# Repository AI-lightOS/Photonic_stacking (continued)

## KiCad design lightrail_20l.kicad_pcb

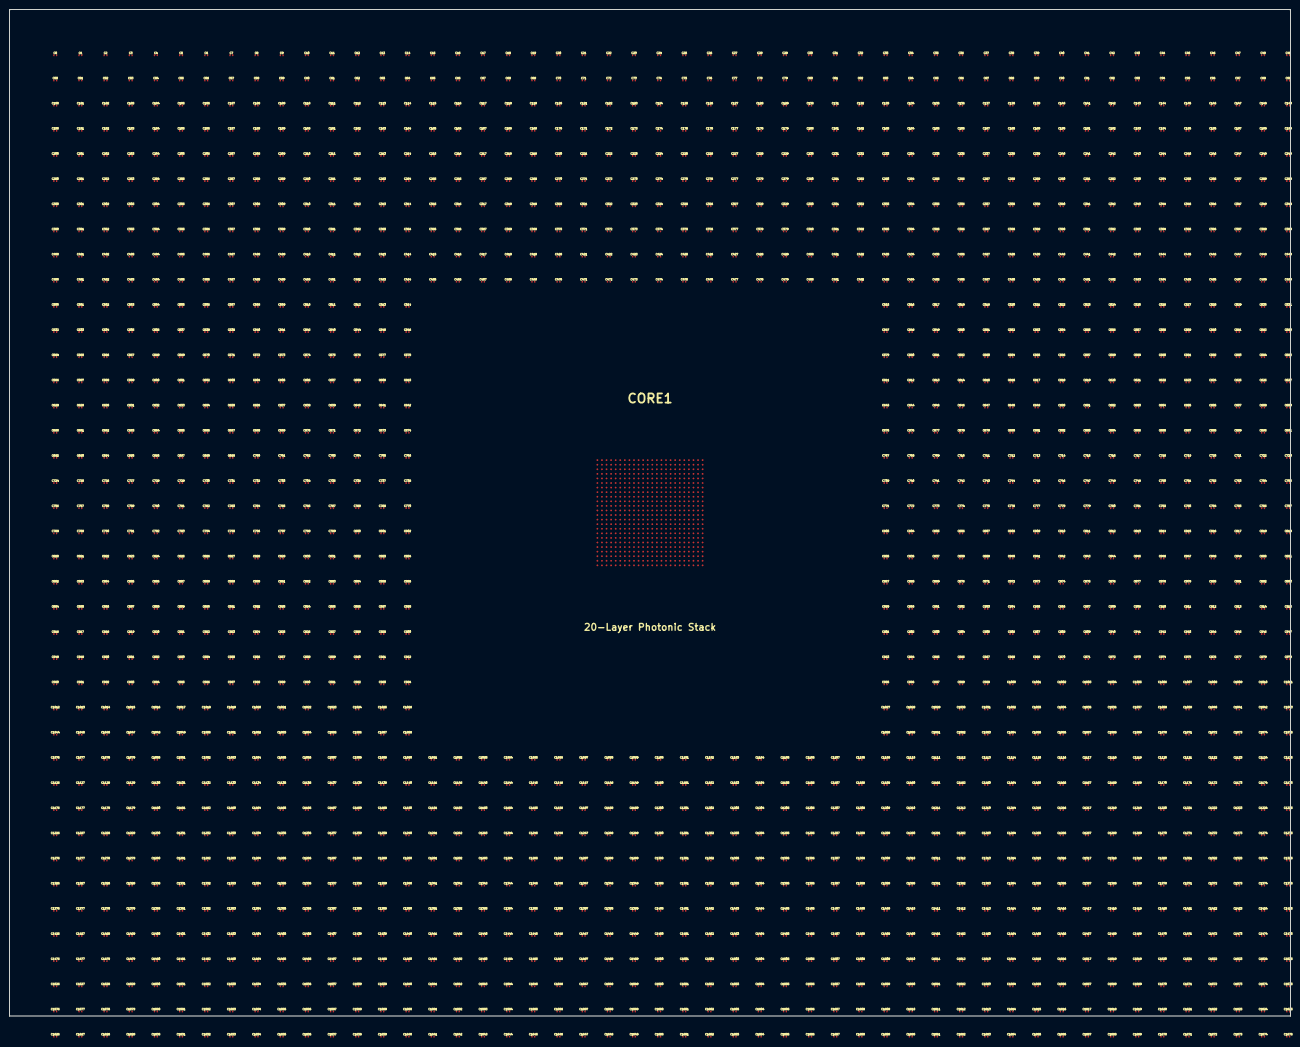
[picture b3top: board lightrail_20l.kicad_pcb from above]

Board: 20 copper layers, 280.0 x 220.0 mm, 1677 parts (0 on the bottom side), 235 nets, no tracks yet.

Parts:
C0, C1, C2, C3, C4, C5, C6, C7, C8, C9, C10, C11, C12, C13, C14, C15, C16, C17, C18, C19, C20, C21, C22, C23, C24, C25, C26, C27, C28, C29, C30, C31, C32, C33, C34, C35, C36, C37, C38, C39, C40, C41, C42, C43, C44, C45, C46, C47, C48, C49, C50, C51, C52, C53, C54, C55, C56, C57, C58, C59, C60, C61, C62, C63, C64, C65, C66, C67, C68, C69, C70, C71, C72, C73, C74, C75, C76, C77, C78, C79, C80, C81, C82, C83, C84, C85, C86, C87, C88, C89, C90, C91, C92, C93, C94, C95, C96, C97, C98, C99, C100, C101, C102, C103, C104, C105, C106, C107, C108, C109, C110, C111, C112, C113, C114, C115, C116, C117, C118, C119, C120, C121, C122, C123, C124, C125, C126, C127, C128, C129, C130, C131, C132, C133, C134, C135, C136, C137, C138, C139, C140, C141, C142, C143, C144, C145, C146, C147, C148, C149, C150, C151, C152, C153, C154, C155, C156, C157, C158, C159, C160, C161, C162, C163, C164, C165, C166, C167, C168, C169, C170, C171, C172, C173, C174, C175, C176, C177, C178, C179, C180, C181, C182, C183, C184, C185, C186, C187, C188, C189, C190, C191, C192, C193, C194, C195, C196, C197, C198, C199, C200, C201, C202, C203, C204, C205, C206, C207, C208, C209, C210, C211, C212, C213, C214, C215, C216, C217, C218, C219, C220, C221, C222, C223, C224, C225, C226, C227, C228, C229, C230, C231, C232, C233, C234, C235, C236, C237, C238, C239, C240, C241, C242, C243, C244, C245, C246, C247, C248, C249, C250, C251, C252, C253, C254, C255, C256, C257, C258, C259, C260, C261, C262, C263, C264, C265, C266, C267, C268, C269, C270, C271, C272, C273, C274, C275, C276, C277, C278, C279, C280, C281, C282, C283, C284, C285, C286, C287, C288, C289, C290, C291, C292, C293, C294, C295, C296, C297, C298, C299, C300, C301, C302, C303, C304, C305, C306, C307, C308, C309, C310, C311, C312, C313, C314, C315, C316, C317, C318, C319, C320, C321, C322, C323, C324, C325, C326, C327, C328, C329, C330, C331, C332, C333, C334, C335, C336, C337, C338, C339, C340, C341, C342, C343, C344, C345, C346, C347, C348, C349, C350, C351, C352, C353, C354, C355, C356, C357, C358, C359, C360, C361, C362, C363, C364, C365, C366, C367, C368, C369, C370, C371, C372, C373, C374, C375, C376, C377, C378, C379, C380, C381, C382, C383, C384, C385, C386, C387, C388, C389, C390, C391, C392, C393, C394, C395, C396, C397, C398, C399, C400, C401, C402, C403, C404, C405, C406, C407, C408, C409, C410, C411, C412, C413, C414, C415, C416, C417, C418, C419, C420, C421, C422, C423, C424, C425, C426, C427, C428, C429, C430, C431, C432, C433, C434, C435, C436, C437, C438, C439, C440, C441, C442, C443, C444, C445, C446, C447, C448, C449, C450, C451, C452, C453, C454, C455, C456, C457, C458, C459, C460, C461, C462, C463, C464, C465, C466, C467, C468, C469, C470, C471, C472, C473, C474, C475, C476, C477, C478, C479, C480, C481, C482, C483, C484, C485, C486, C487, C488, C489, C490, C491, C492, C493, C494, C495, C496, C497, C498, C499, C500, C501, C502, C503, C504, C505, C506, C507, C508, C509, C510, C511, C512, C513, C514, C515, C516, C517, C518, C519, C520, C521, C522, C523, C524, C525, C526, C527, C528, C529, C530, C531, C532, C533, C534, C535, C536, C537, C538, C539, C540, C541, C542, C543, C544, C545, C546, C547, C548, C549, C550, C551, C552, C553, C554, C555, C556, C557, C558, C559, C560, C561, C562, C563, C564, C565, C566, C567, C568, C569, C570, C571, C572, C573, C574, C575, C576, C577, C578, C579, C580, C581, C582, C583, C584, C585, C586, C587, C588, C589, C590, C591, C592, C593, C594, C595, C596, C597, C598, C599, C600, C601, C602, C603, C604, C605, C606, C607, C608, C609, C610, C611, C612, C613, C614, C615, C616, C617, C618, C619, C620, C621, C622, C623, C624, C625, C626, C627, C628, C629, C630, C631, C632, C633, C634, C635, C636, C637, C638, C639, C640, C641, C642, C643, C644, C645, C646, C647, C648, C649, C650, C651, C652, C653, C654, C655, C656, C657, C658, C659, C660, C661, C662, C663, C664, C665, C666, C667, C668, C669, C670, C671, C672, C673, C674, C675, C676, C677, C678, C679, C680, C681, C682, C683, C684, C685, C686, C687, C688, C689, C690, C691, C692, C693, C694, C695, C696, C697, C698, C699, C700, C701, C702, C703, C704, C705, C706, C707, C708, C709, C710, C711, C712, C713, C714, C715, C716, C717, C718, C719, C720, C721, C722, C723, C724, C725, C726, C727, C728, C729, C730, C731, C732, C733, C734, C735, C736, C737, C738, C739, C740, C741, C742, C743, C744, C745, C746, C747, C748, C749, C750, C751, C752, C753, C754, C755, C756, C757, C758, C759, C760, C761, C762, C763, C764, C765, C766, C767, C768, C769, C770, C771, C772, C773, C774, C775, C776, C777, C778, C779, C780, C781, C782, C783, C784, C785, C786, C787, C788, C789, C790, C791, C792, C793, C794, C795, C796, C797, C798, C799, C800, C801, C802, C803, C804, C805, C806, C807, C808, C809, C810, C811, C812, C813, C814, C815, C816, C817, C818, C819, C820, C821, C822, C823, C824, C825, C826, C827, C828, C829, C830, C831, C832, C833, C834, C835, C836, C837, C838, C839, C840, C841, C842, C843, C844, C845, C846, C847, C848, C849, C850, C851, C852, C853, C854, C855, C856, C857, C858, C859, C860, C861, C862, C863, C864, C865, C866, C867, C868, C869, C870, C871, C872, C873, C874, C875, C876, C877, C878, C879, C880, C881, C882, C883, C884, C885, C886, C887, C888, C889, C890, C891, C892, C893, C894, C895, C896, C897, C898, C899, C900, C901, C902, C903, C904, C905, C906, C907, C908, C909, C910, C911, C912, C913, C914, C915, C916, C917, C918, C919, C920, C921, C922, C923, C924, C925, C926, C927, C928, C929, C930, C931, C932, C933, C934, C935, C936, C937, C938, C939, C940, C941, C942, C943, C944, C945, C946, C947, C948, C949, C950, C951, C952, C953, C954, C955, C956, C957, C958, C959, C960, C961, C962, C963, C964, C965, C966, C967, C968, C969, C970, C971, C972, C973, C974, C975, C976, C977, C978, C979, C980, C981, C982, C983, C984, C985, C986, C987, C988, C989, C990, C991, C992, C993, C994, C995, C996, C997, C998, C999, C1000, C1001, C1002, C1003, C1004, C1005, C1006, C1007, C1008, C1009, C1010, C1011, C1012, C1013, C1014, C1015, C1016, C1017, C1018, C1019, C1020, C1021, C1022, C1023, C1024, C1025, C1026, C1027, C1028, C1029, C1030, C1031, C1032, C1033, C1034, C1035, C1036, C1037, C1038, C1039, C1040, C1041, C1042, C1043, C1044, C1045, C1046, C1047, C1048, C1049, C1050, C1051, C1052, C1053, C1054, C1055, C1056, C1057, C1058, C1059, C1060, C1061, C1062, C1063, C1064, C1065, C1066, C1067, C1068, C1069, C1070, C1071, C1072, C1073, C1074, C1075, C1076, C1077, C1078, C1079, C1080, C1081, C1082, C1083, C1084, C1085, C1086, C1087, C1088, C1089, C1090, C1091, C1092, C1093, C1094, C1095, C1096, C1097, C1098, C1099, C1100, C1101, C1102, C1103, C1104, C1105, C1106, C1107, C1108, C1109, C1110, C1111, C1112, C1113, C1114, C1115, C1116, C1117, C1118, C1119, C1120, C1121, C1122, C1123, C1124, C1125, C1126, C1127, C1128, C1129, C1130, C1131, C1132, C1133, C1134, C1135, C1136, C1137, C1138, C1139, C1140, C1141, C1142, C1143, C1144, C1145, C1146, C1147, C1148, C1149, C1150, C1151, C1152, C1153, C1154, C1155, C1156, C1157, C1158, C1159, C1160, C1161, C1162, C1163, C1164, C1165, C1166, C1167, C1168, C1169, C1170, C1171, C1172, C1173, C1174, C1175, C1176, C1177, C1178, C1179, C1180, C1181, C1182, C1183, C1184, C1185, C1186, C1187, C1188, C1189, C1190, C1191, C1192, C1193, C1194, C1195, C1196, C1197, C1198, C1199, C1200, C1201, C1202, C1203, C1204, C1205, C1206, C1207, C1208, C1209, C1210, C1211, C1212, C1213, C1214, C1215, C1216, C1217, C1218, C1219, C1220, C1221, C1222, C1223, C1224, C1225, C1226, C1227, C1228, C1229, C1230, C1231, C1232, C1233, C1234, C1235, C1236, C1237, C1238, C1239, C1240, C1241, C1242, C1243, C1244, C1245, C1246, C1247, C1248, C1249, C1250, C1251, C1252, C1253, C1254, C1255, C1256, C1257, C1258, C1259, C1260, C1261, C1262, C1263, C1264, C1265, C1266, C1267, C1268, C1269, C1270, C1271, C1272, C1273, C1274, C1275, C1276, C1277, C1278, C1279, C1280, C1281, C1282, C1283, C1284, C1285, C1286, C1287, C1288, C1289, C1290, C1291, C1292, C1293, C1294, C1295, C1296, C1297, C1298, C1299, C1300, C1301, C1302, C1303, C1304, C1305, C1306, C1307, C1308, C1309, C1310, C1311, C1312, C1313, C1314, C1315, C1316, C1317, C1318, C1319, C1320, C1321, C1322, C1323, C1324, C1325, C1326, C1327, C1328, C1329, C1330, C1331, C1332, C1333, C1334, C1335, C1336, C1337, C1338, C1339, C1340, C1341, C1342, C1343, C1344, C1345, C1346, C1347, C1348, C1349, C1350, C1351, C1352, C1353, C1354, C1355, C1356, C1357, C1358, C1359, C1360, C1361, C1362, C1363, C1364, C1365, C1366, C1367, C1368, C1369, C1370, C1371, C1372, C1373, C1374, C1375, C1376, C1377, C1378, C1379, C1380, C1381, C1382, C1383, C1384, C1385, C1386, C1387, C1388, C1389, C1390, C1391, C1392, C1393, C1394, C1395, C1396, C1397, C1398, C1399, C1400, C1401, C1402, C1403, C1404, C1405, C1406, C1407, C1408, C1409, C1410, C1411, C1412, C1413, C1414, C1415, C1416, C1417, C1418, C1419, C1420, C1421, C1422, C1423, C1424, C1425, C1426, C1427, C1428, C1429, C1430, C1431, C1432, C1433, C1434, C1435, C1436, C1437, C1438, C1439, C1440, C1441, C1442, C1443, C1444, C1445, C1446, C1447, C1448, C1449, C1450, C1451, C1452, C1453, C1454, C1455, C1456, C1457, C1458, C1459, C1460, C1461, C1462, C1463, C1464, C1465, C1466, C1467, C1468, C1469, C1470, C1471, C1472, C1473, C1474, C1475, C1476, C1477, C1478, C1479, C1480, C1481, C1482, C1483, C1484, C1485, C1486, C1487, C1488, C1489, C1490, C1491, C1492, C1493, C1494, C1495, C1496, C1497, C1498, C1499, C1500, C1501, C1502, C1503, C1504, C1505, C1506, C1507, C1508, C1509, C1510, C1511, C1512, C1513, C1514, C1515, C1516, C1517, C1518, C1519, C1520, C1521, C1522, C1523, C1524, C1525, C1526, C1527, C1528, C1529, C1530, C1531, C1532, C1533, C1534, C1535, C1536, C1537, C1538, C1539, C1540, C1541, C1542, C1543, C1544, C1545, C1546, C1547, C1548, C1549, C1550, C1551, C1552, C1553, C1554, C1555, C1556, C1557, C1558, C1559, C1560, C1561, C1562, C1563, C1564, C1565, C1566, C1567, C1568, C1569, C1570, C1571, C1572, C1573, C1574, C1575, C1576, C1577, C1578, C1579, C1580, C1581, C1582, C1583, C1584, C1585, C1586, C1587, C1588, C1589, C1590, C1591, C1592, C1593, C1594, C1595, C1596, C1597, C1598, C1599, C1600, C1601, C1602, C1603, C1604, C1605, C1606, C1607, C1608, C1609, C1610, C1611, C1612, C1613, C1614, C1615, C1616, C1617, C1618, C1619, C1620, C1621, C1622, C1623, C1624, C1625, C1626, C1627, C1628, C1629, C1630, C1631, C1632, C1633, C1634, C1635, C1636, C1637, C1638, C1639, C1640, C1641, C1642, C1643, C1644, C1645, C1646, C1647, C1648, C1649, C1650, C1651, C1652, C1653, C1654, C1655, C1656, C1657, C1658, C1659, C1660, C1661, C1662, C1663, C1664, C1665, C1666, C1667, C1668, C1669, C1670, C1671, C1672, C1673, C1674, C1675: C_0201_0603Metric
CORE1: 20-Layer Photonic Stack; IntelligenceStack_20L

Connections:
GND: C0.2, C1.1, C1.2, C2.2, C3.2, C4.2, C5.1, C5.2, C6.2, C7.2, C8.2, C9.1, C9.2, C10.1, C10.2, C11.1, C11.2, C12.2, C13.2, C14.2, C15.1, C15.2, C16.1, C16.2, C17.2, C18.2, C19.1, C19.2, C20.1, C20.2, C21.1, C21.2, C22.2, C23.1, C23.2, C24.2, C25.2, C26.1, C26.2, C27.2, C28.2, C29.2, C30.2, C31.2, C32.2, C33.2, C34.2, C35.1, C35.2, C36.1, C36.2, C37.1, C37.2, C38.1, C38.2, C39.2, C40.2, C41.2, C42.2, C43.2, C44.1, C44.2, C45.1, C45.2, C46.2, C47.1, C47.2, C48.2, C49.2, C50.1, C50.2, C51.2, C52.2, C53.2, C54.2, C55.1, C55.2, C56.1, C56.2, C57.2, C58.1, C58.2, C59.2, C60.2, C61.2, C62.1, C62.2, C63.2, C64.2, C65.1, C65.2, C66.2, C67.1, C67.2, C68.2, C69.1, C69.2, C70.2, C71.1, C71.2, C72.2, C73.2, C74.2, C75.2, C76.2, C77.1, C77.2, C78.2, C79.2, C80.2, C81.2, C82.1, C82.2, C83.2, C84.2, C85.2, C86.2, C87.2, C88.1, C88.2, C89.2, C90.2, C91.2, C92.1, C92.2, C93.2, C94.1, C94.2, C95.1, C95.2, C96.2, C97.2, C98.1, C98.2, C99.2, C100.2, C101.2, C102.2, C103.2, C104.1, C104.2, C105.2, C106.1, C106.2, C107.1, C107.2, C108.1, C108.2, C109.1, C109.2, C110.2, C111.2, C112.1, C112.2, C113.2, C114.2, C115.1, C115.2, C116.1, C116.2, C117.2, C118.2, C119.1, C119.2, C120.2, C121.2, C122.1, C122.2, C123.2, C124.1, C124.2, C125.2, C126.2, C127.1, C127.2, C128.2, C129.2, C130.2, C131.1, C131.2, C132.2, C133.2, C134.2, C135.2, C136.2, C137.2, C138.1, C138.2, C139.2, C140.1, C140.2, C141.2, C142.2, C143.1, C143.2, C144.2, C145.2, C146.1, C146.2, C147.2, C148.2, C149.2, C150.1, C150.2, C151.2, C152.1, C152.2, C153.1, C153.2, C154.2, C155.2, C156.2, C157.2, C158.2, C159.1, C159.2, C160.2, C161.1, C161.2, C162.2, C163.2, C164.2, C165.2, C166.2, C167.2, C168.2, C169.1, C169.2, C170.1, C170.2, C171.2, C172.2, C173.2, C174.2, C175.2, C176.2, C177.2, C178.2, C179.2, C180.2, C181.2, C182.2, C183.1, C183.2, C184.2, C185.2, C186.2, C187.1, C187.2, C188.1, C188.2, C189.1, C189.2, C190.1, C190.2, C191.2, C192.2, C193.2, C194.2, C195.2, C196.1, C196.2, C197.2, C198.2, C199.2, C200.1, C200.2, C201.1, C201.2, C202.2, C203.2, C204.2, C205.2, C206.2, C207.2, C208.2, C209.1, C209.2, C210.2, C211.2, C212.1, C212.2, C213.1, C213.2, C214.2, C215.2, C216.2, C217.1, C217.2, C218.1, C218.2, C219.2, C220.2, C221.2, C222.2, C223.2, C224.1, C224.2, C225.2, C226.2, C227.2, C228.2, C229.2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
V_ANALOG: C2.1, C4.1, C6.1, C7.1, C8.1, C13.1, C14.1, C17.1, C22.1, C31.1, C32.1, C33.1, C41.1, C48.1, C49.1, C52.1, C54.1, C61.1, C64.1, C68.1, C70.1, C72.1, C73.1, C74.1, C76.1, C79.1, C80.1, C81.1, C83.1, C87.1, C90.1, C96.1, C97.1, C99.1, C100.1, C105.1, C113.1, C118.1, C126.1, C129.1, C133.1, C139.1, C141.1, C142.1, C145.1, C149.1, C151.1, C154.1, C155.1, C156.1, C157.1, C158.1, C160.1, C162.1, C165.1, C166.1, C167.1, C168.1, C177.1, C178.1, C179.1, C180.1, C181.1, C185.1, C191.1, C195.1, C197.1, C198.1, C199.1, C205.1, C207.1, C208.1, C210.1, C214.1, C215.1, C219.1, C220.1, C221.1, C222.1, C225.1, C226.1, C228.1, C234.1, C235.1, C240.1, C241.1, C245.1, C255.1, C256.1, C259.1, C266.1, C269.1, C271.1, C275.1, C277.1, C278.1, C280.1, C282.1, C289.1, C290.1, C295.1, C299.1, C308.1, C310.1, C313.1, C314.1, C315.1, C316.1, C319.1, C322.1, C323.1, C327.1, C345.1, C346.1, C348.1, C351.1, C353.1, C358.1, C359.1, C360.1, C361.1, C364.1, C365.1, C367.1, C368.1, C371.1, C372.1, C375.1, C376.1, C378.1, C379.1, C380.1, C383.1, C385.1, C391.1, C393.1, C394.1, C397.1, C399.1, C400.1, C401.1, C402.1, C404.1, C405.1, C407.1, C409.1, C410.1, C414.1, C415.1, C418.1, C420.1, C424.1, C427.1, C428.1, C431.1, C434.1, C437.1, C441.1, C443.1, C444.1, C445.1, C451.1, C453.1, C461.1, C466.1, C467.1, C468.1, C473.1, C479.1, C481.1, C485.1, C486.1, C490.1, C491.1, C493.1, C498.1, C501.1, C502.1, C505.1, C506.1, C509.1, C510.1, C513.1, C514.1, C521.1, C522.1, C523.1, C525.1, C535.1, C536.1, C539.1, C544.1, C546.1, C548.1, C559.1, C560.1, C562.1, C563.1, C567.1, C574.1, C575.1, C576.1, C579.1, C580.1, C581.1, C584.1, C585.1, C588.1, C590.1, C592.1, C593.1, C598.1, C599.1, C601.1, C604.1, C605.1, C611.1, C614.1, C616.1, C624.1, C627.1, C633.1, C634.1, C639.1, C640.1, C642.1, C644.1, C646.1, C647.1, C649.1, C653.1, C654.1, C659.1, C660.1, C661.1, C665.1, C669.1, C677.1, C679.1, C680.1, C681.1, C684.1, C685.1, C688.1, C689.1, C691.1, C692.1, C693.1, C695.1, C696.1, C703.1, C704.1, C706.1, C710.1, C714.1, C715.1, C717.1, C719.1, C722.1, C725.1, C726.1, C730.1, C731.1, C735.1, C745.1, C748.1, C752.1, C755.1, C756.1, C758.1, C759.1, C772.1, C775.1, C782.1, C785.1, C788.1, C793.1, C796.1, C797.1, C799.1, C802.1, C803.1, C804.1, C810.1, C813.1, C818.1, C819.1, C821.1, C827.1, C833.1, C835.1, C836.1, C837.1, C844.1, C847.1, C849.1, C850.1, C851.1, C852.1, C854.1, C857.1, C859.1, C863.1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
V_LIGHT: C0.1, C3.1, C12.1, C18.1, C24.1, C25.1, C27.1, C28.1, C29.1, C30.1, C34.1, C39.1, C40.1, C42.1, C43.1, C46.1, C51.1, C53.1, C57.1, C59.1, C60.1, C63.1, C66.1, C75.1, C78.1, C84.1, C85.1, C86.1, C89.1, C91.1, C93.1, C101.1, C102.1, C103.1, C110.1, C111.1, C114.1, C117.1, C120.1, C121.1, C123.1, C125.1, C128.1, C130.1, C132.1, C134.1, C135.1, C136.1, C137.1, C144.1, C147.1, C148.1, C163.1, C164.1, C171.1, C172.1, C173.1, C174.1, C175.1, C176.1, C182.1, C184.1, C186.1, C192.1, C193.1, C194.1, C202.1, C203.1, C204.1, C206.1, C211.1, C216.1, C223.1, C227.1, C229.1, C230.1, C231.1, C232.1, C233.1, C242.1, C246.1, C247.1, C249.1, C251.1, C253.1, C257.1, C258.1, C261.1, C263.1, C265.1, C268.1, C270.1, C272.1, C273.1, C276.1, C285.1, C286.1, C288.1, C292.1, C297.1, C298.1, C300.1, C302.1, C304.1, C306.1, C312.1, C317.1, C321.1, C325.1, C326.1, C328.1, C330.1, C331.1, C332.1, C335.1, C336.1, C337.1, C338.1, C341.1, C342.1, C343.1, C344.1, C347.1, C350.1, C355.1, C357.1, C363.1, C369.1, C381.1, C382.1, C384.1, C388.1, C390.1, C396.1, C403.1, C406.1, C408.1, C411.1, C423.1, C425.1, C426.1, C430.1, C432.1, C433.1, C435.1, C436.1, C446.1, C447.1, C452.1, C456.1, C457.1, C458.1, C460.1, C462.1, C463.1, C464.1, C469.1, C471.1, C474.1, C475.1, C476.1, C477.1, C480.1, C483.1, C487.1, C492.1, C494.1, C495.1, C497.1, C500.1, C503.1, C507.1, C511.1, C512.1, C515.1, C519.1, C520.1, C524.1, C528.1, C529.1, C531.1, C534.1, C538.1, C543.1, C549.1, C551.1, C552.1, C553.1, C555.1, C556.1, C558.1, C561.1, C564.1, C565.1, C566.1, C569.1, C572.1, C577.1, C578.1, C582.1, C586.1, C587.1, C600.1, C603.1, C606.1, C607.1, C613.1, C617.1, C618.1, C621.1, C622.1, C623.1, C625.1, C629.1, C635.1, C637.1, C641.1, C645.1, C648.1, C650.1, C651.1, C655.1, C656.1, C657.1, C658.1, C666.1, C667.1, C668.1, C670.1, C672.1, C673.1, C674.1, C675.1, C678.1, C682.1, C683.1, C698.1, C699.1, C701.1, C707.1, C709.1, C711.1, C713.1, C720.1, C721.1, C723.1, C724.1, C727.1, C728.1, C729.1, C732.1, C733.1, C734.1, C737.1, C738.1, C740.1, C743.1, C746.1, C751.1, C757.1, C762.1, C763.1, C764.1, C765.1, C770.1, C771.1, C773.1, C776.1, C777.1, C778.1, C779.1, C780.1, C781.1, C798.1, C805.1, C806.1, C809.1, C812.1, C814.1, C815.1, C816.1, C817.1, C825.1, C826.1, C830.1, C832.1, C834.1, C840.1, C843.1, C848.1, C853.1, C855.1, C856.1, C862.1, C864.1, C865.1, C877.1, C878.1, C881.1, C882.1, C886.1, C887.1, C890.1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
WAVE_BUS_0: CORE1.1, CORE1.257, CORE1.513
WAVE_BUS_1: CORE1.2, CORE1.258, CORE1.514
WAVE_BUS_2: CORE1.3, CORE1.259, CORE1.515
WAVE_BUS_3: CORE1.4, CORE1.260, CORE1.516
WAVE_BUS_4: CORE1.5, CORE1.261, CORE1.517
WAVE_BUS_5: CORE1.6, CORE1.262, CORE1.518
WAVE_BUS_6: CORE1.7, CORE1.263, CORE1.519
WAVE_BUS_7: CORE1.8, CORE1.264, CORE1.520
WAVE_BUS_8: CORE1.9, CORE1.265, CORE1.521
WAVE_BUS_9: CORE1.10, CORE1.266, CORE1.522
WAVE_BUS_10: CORE1.11, CORE1.267, CORE1.523
WAVE_BUS_11: CORE1.12, CORE1.268, CORE1.524
WAVE_BUS_12: CORE1.13, CORE1.269, CORE1.525
WAVE_BUS_13: CORE1.14, CORE1.270, CORE1.526
WAVE_BUS_14: CORE1.15, CORE1.271, CORE1.527
WAVE_BUS_15: CORE1.16, CORE1.272, CORE1.528
WAVE_BUS_16: CORE1.17, CORE1.273, CORE1.529
WAVE_BUS_17: CORE1.18, CORE1.530
WAVE_BUS_18: CORE1.19, CORE1.531
WAVE_BUS_19: CORE1.20, CORE1.532
WAVE_BUS_20: CORE1.21, CORE1.533
WAVE_BUS_21: CORE1.22, CORE1.534
WAVE_BUS_22: CORE1.23, CORE1.535
WAVE_BUS_23: CORE1.24, CORE1.280, CORE1.536
WAVE_BUS_24: CORE1.25, CORE1.281, CORE1.537
WAVE_BUS_25: CORE1.26, CORE1.282, CORE1.538
WAVE_BUS_26: CORE1.27, CORE1.283, CORE1.539
WAVE_BUS_27: CORE1.28, CORE1.284, CORE1.540
WAVE_BUS_28: CORE1.29, CORE1.285, CORE1.541
WAVE_BUS_29: CORE1.30, CORE1.286, CORE1.542
WAVE_BUS_30: CORE1.31, CORE1.287, CORE1.543
WAVE_BUS_31: CORE1.32, CORE1.288, CORE1.544
WAVE_BUS_32: CORE1.33, CORE1.289, CORE1.545
WAVE_BUS_33: CORE1.34, CORE1.290, CORE1.546
WAVE_BUS_34: CORE1.35, CORE1.291, CORE1.547
WAVE_BUS_35: CORE1.36, CORE1.292, CORE1.548
WAVE_BUS_36: CORE1.37, CORE1.293, CORE1.549
WAVE_BUS_37: CORE1.38, CORE1.294, CORE1.550
WAVE_BUS_38: CORE1.39, CORE1.295, CORE1.551
WAVE_BUS_39: CORE1.40, CORE1.296, CORE1.552
WAVE_BUS_40: CORE1.41, CORE1.297, CORE1.553
WAVE_BUS_41: CORE1.42, CORE1.554
WAVE_BUS_42: CORE1.43, CORE1.555
WAVE_BUS_43: CORE1.44, CORE1.556
WAVE_BUS_44: CORE1.45, CORE1.557
WAVE_BUS_45: CORE1.46, CORE1.558
WAVE_BUS_46: CORE1.47, CORE1.559
WAVE_BUS_47: CORE1.48, CORE1.304, CORE1.560
WAVE_BUS_48: CORE1.49, CORE1.305, CORE1.561
WAVE_BUS_49: CORE1.50, CORE1.306, CORE1.562
WAVE_BUS_50: CORE1.51, CORE1.307, CORE1.563
WAVE_BUS_51: CORE1.52, CORE1.308, CORE1.564
WAVE_BUS_52: CORE1.53, CORE1.309, CORE1.565
WAVE_BUS_53: CORE1.54, CORE1.310, CORE1.566
WAVE_BUS_54: CORE1.55, CORE1.311, CORE1.567
WAVE_BUS_55: CORE1.56, CORE1.312, CORE1.568
WAVE_BUS_56: CORE1.57, CORE1.313, CORE1.569
WAVE_BUS_57: CORE1.58, CORE1.314, CORE1.570
WAVE_BUS_58: CORE1.59, CORE1.315, CORE1.571
WAVE_BUS_59: CORE1.60, CORE1.316, CORE1.572
WAVE_BUS_60: CORE1.61, CORE1.317, CORE1.573
WAVE_BUS_61: CORE1.62, CORE1.318, CORE1.574
WAVE_BUS_62: CORE1.63, CORE1.319, CORE1.575
WAVE_BUS_63: CORE1.64, CORE1.320, CORE1.576
WAVE_BUS_64: CORE1.65, CORE1.321
WAVE_BUS_71: CORE1.72, CORE1.328
WAVE_BUS_72: CORE1.73, CORE1.329
WAVE_BUS_73: CORE1.74, CORE1.330
WAVE_BUS_74: CORE1.75, CORE1.331
WAVE_BUS_75: CORE1.76, CORE1.332
WAVE_BUS_76: CORE1.77, CORE1.333
WAVE_BUS_77: CORE1.78, CORE1.334
WAVE_BUS_78: CORE1.79, CORE1.335
WAVE_BUS_79: CORE1.80, CORE1.336
WAVE_BUS_80: CORE1.81, CORE1.337
WAVE_BUS_81: CORE1.82, CORE1.338
WAVE_BUS_82: CORE1.83, CORE1.339
WAVE_BUS_83: CORE1.84, CORE1.340
WAVE_BUS_84: CORE1.85, CORE1.341
WAVE_BUS_85: CORE1.86, CORE1.342
WAVE_BUS_86: CORE1.87, CORE1.343
WAVE_BUS_87: CORE1.88, CORE1.344
WAVE_BUS_88: CORE1.89, CORE1.345
WAVE_BUS_95: CORE1.96, CORE1.352
WAVE_BUS_96: CORE1.97, CORE1.353
WAVE_BUS_97: CORE1.98, CORE1.354
WAVE_BUS_98: CORE1.99, CORE1.355
WAVE_BUS_99: CORE1.100, CORE1.356
WAVE_BUS_100: CORE1.101, CORE1.357
WAVE_BUS_101: CORE1.102, CORE1.358
WAVE_BUS_102: CORE1.103, CORE1.359
WAVE_BUS_103: CORE1.104, CORE1.360
WAVE_BUS_104: CORE1.105, CORE1.361
WAVE_BUS_105: CORE1.106, CORE1.362
WAVE_BUS_106: CORE1.107, CORE1.363
WAVE_BUS_107: CORE1.108, CORE1.364
WAVE_BUS_108: CORE1.109, CORE1.365
WAVE_BUS_109: CORE1.110, CORE1.366
WAVE_BUS_110: CORE1.111, CORE1.367
WAVE_BUS_111: CORE1.112, CORE1.368
WAVE_BUS_112: CORE1.113, CORE1.369
WAVE_BUS_113: CORE1.114, CORE1.370
WAVE_BUS_114: CORE1.115, CORE1.371
WAVE_BUS_115: CORE1.116, CORE1.372
WAVE_BUS_116: CORE1.117, CORE1.373
WAVE_BUS_117: CORE1.118, CORE1.374
WAVE_BUS_118: CORE1.119, CORE1.375
WAVE_BUS_119: CORE1.120, CORE1.376
WAVE_BUS_120: CORE1.121, CORE1.377
WAVE_BUS_121: CORE1.122, CORE1.378
WAVE_BUS_122: CORE1.123, CORE1.379
WAVE_BUS_123: CORE1.124, CORE1.380
WAVE_BUS_124: CORE1.125, CORE1.381
WAVE_BUS_125: CORE1.126, CORE1.382
WAVE_BUS_126: CORE1.127, CORE1.383
WAVE_BUS_127: CORE1.128, CORE1.384
WAVE_BUS_128: CORE1.129, CORE1.385
WAVE_BUS_129: CORE1.130, CORE1.386
WAVE_BUS_130: CORE1.131, CORE1.387
WAVE_BUS_131: CORE1.132, CORE1.388
WAVE_BUS_132: CORE1.133, CORE1.389
WAVE_BUS_133: CORE1.134, CORE1.390
WAVE_BUS_134: CORE1.135, CORE1.391
WAVE_BUS_135: CORE1.136, CORE1.392
WAVE_BUS_136: CORE1.137, CORE1.393
WAVE_BUS_137: CORE1.138, CORE1.394
WAVE_BUS_138: CORE1.139, CORE1.395
WAVE_BUS_139: CORE1.140, CORE1.396
WAVE_BUS_140: CORE1.141, CORE1.397
WAVE_BUS_141: CORE1.142, CORE1.398
WAVE_BUS_142: CORE1.143, CORE1.399
WAVE_BUS_143: CORE1.144, CORE1.400
WAVE_BUS_144: CORE1.145, CORE1.401
WAVE_BUS_145: CORE1.146, CORE1.402
WAVE_BUS_146: CORE1.147, CORE1.403
WAVE_BUS_147: CORE1.148, CORE1.404
WAVE_BUS_148: CORE1.149, CORE1.405
WAVE_BUS_149: CORE1.150, CORE1.406
WAVE_BUS_150: CORE1.151, CORE1.407
WAVE_BUS_151: CORE1.152, CORE1.408
WAVE_BUS_152: CORE1.153, CORE1.409
WAVE_BUS_153: CORE1.154, CORE1.410
WAVE_BUS_154: CORE1.155, CORE1.411
WAVE_BUS_155: CORE1.156, CORE1.412
WAVE_BUS_156: CORE1.157, CORE1.413
WAVE_BUS_157: CORE1.158, CORE1.414
WAVE_BUS_158: CORE1.159, CORE1.415
WAVE_BUS_159: CORE1.160, CORE1.416
WAVE_BUS_160: CORE1.161, CORE1.417
WAVE_BUS_161: CORE1.162, CORE1.418
WAVE_BUS_162: CORE1.163, CORE1.419
WAVE_BUS_163: CORE1.164, CORE1.420
WAVE_BUS_164: CORE1.165, CORE1.421
WAVE_BUS_165: CORE1.166, CORE1.422
WAVE_BUS_166: CORE1.167, CORE1.423
WAVE_BUS_167: CORE1.168, CORE1.424
WAVE_BUS_168: CORE1.169, CORE1.425
WAVE_BUS_169: CORE1.170, CORE1.426
WAVE_BUS_170: CORE1.171, CORE1.427
WAVE_BUS_171: CORE1.172, CORE1.428
WAVE_BUS_172: CORE1.173, CORE1.429
WAVE_BUS_173: CORE1.174, CORE1.430
WAVE_BUS_174: CORE1.175, CORE1.431
WAVE_BUS_175: CORE1.176, CORE1.432
WAVE_BUS_176: CORE1.177, CORE1.433
WAVE_BUS_177: CORE1.178, CORE1.434
WAVE_BUS_178: CORE1.179, CORE1.435
WAVE_BUS_179: CORE1.180, CORE1.436
WAVE_BUS_180: CORE1.181, CORE1.437
WAVE_BUS_181: CORE1.182, CORE1.438
WAVE_BUS_182: CORE1.183, CORE1.439
WAVE_BUS_183: CORE1.184, CORE1.440
WAVE_BUS_184: CORE1.185, CORE1.441
WAVE_BUS_185: CORE1.186, CORE1.442
WAVE_BUS_186: CORE1.187, CORE1.443
WAVE_BUS_187: CORE1.188, CORE1.444
WAVE_BUS_188: CORE1.189, CORE1.445
WAVE_BUS_189: CORE1.190, CORE1.446
WAVE_BUS_190: CORE1.191, CORE1.447
WAVE_BUS_191: CORE1.192, CORE1.448
WAVE_BUS_192: CORE1.193, CORE1.449
WAVE_BUS_193: CORE1.194, CORE1.450
WAVE_BUS_194: CORE1.195, CORE1.451
WAVE_BUS_195: CORE1.196, CORE1.452
WAVE_BUS_196: CORE1.197, CORE1.453
WAVE_BUS_197: CORE1.198, CORE1.454
WAVE_BUS_198: CORE1.199, CORE1.455
WAVE_BUS_199: CORE1.200, CORE1.456
WAVE_BUS_200: CORE1.201, CORE1.457
WAVE_BUS_201: CORE1.202, CORE1.458
WAVE_BUS_202: CORE1.203, CORE1.459
WAVE_BUS_203: CORE1.204, CORE1.460
WAVE_BUS_204: CORE1.205, CORE1.461
WAVE_BUS_205: CORE1.206, CORE1.462
WAVE_BUS_206: CORE1.207, CORE1.463
WAVE_BUS_207: CORE1.208, CORE1.464
WAVE_BUS_208: CORE1.209, CORE1.465
WAVE_BUS_209: CORE1.210, CORE1.466
WAVE_BUS_210: CORE1.211, CORE1.467
WAVE_BUS_211: CORE1.212, CORE1.468
WAVE_BUS_212: CORE1.213, CORE1.469
WAVE_BUS_213: CORE1.214, CORE1.470
WAVE_BUS_214: CORE1.215, CORE1.471
WAVE_BUS_215: CORE1.216, CORE1.472
WAVE_BUS_216: CORE1.217, CORE1.473
WAVE_BUS_217: CORE1.218, CORE1.474
WAVE_BUS_218: CORE1.219, CORE1.475
WAVE_BUS_219: CORE1.220, CORE1.476
WAVE_BUS_220: CORE1.221, CORE1.477
WAVE_BUS_221: CORE1.222, CORE1.478
WAVE_BUS_222: CORE1.223, CORE1.479
WAVE_BUS_223: CORE1.224, CORE1.480
WAVE_BUS_224: CORE1.225, CORE1.481
WAVE_BUS_231: CORE1.232, CORE1.488
WAVE_BUS_232: CORE1.233, CORE1.489
WAVE_BUS_233: CORE1.234, CORE1.490
WAVE_BUS_234: CORE1.235, CORE1.491
WAVE_BUS_235: CORE1.236, CORE1.492
WAVE_BUS_236: CORE1.237, CORE1.493
WAVE_BUS_237: CORE1.238, CORE1.494
WAVE_BUS_238: CORE1.239, CORE1.495
WAVE_BUS_239: CORE1.240, CORE1.496
WAVE_BUS_240: CORE1.241, CORE1.497
WAVE_BUS_241: CORE1.242, CORE1.498
WAVE_BUS_242: CORE1.243, CORE1.499
WAVE_BUS_243: CORE1.244, CORE1.500
WAVE_BUS_244: CORE1.245, CORE1.501
WAVE_BUS_245: CORE1.246, CORE1.502
WAVE_BUS_246: CORE1.247, CORE1.503
WAVE_BUS_247: CORE1.248, CORE1.504
WAVE_BUS_248: CORE1.249, CORE1.505
WAVE_BUS_255: CORE1.256, CORE1.512

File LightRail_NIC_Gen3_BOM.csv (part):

Designator,Description,Manufacturer,MPN,Qty,Footprint
U1,TFLN-MZM-400G-C Modulator Array,LightRail-Optical,LR-TFLN-MZM-400G,1,TFLN_MZM_400G
U2,DFB Laser Source (CW-C-Band),Lumentum,LR-DFB-C-BAND,1,DFB_Laser_U2
U3,Sub-micron Waveguide Routing Core,LightRail-Silicon,LR-OPT-CORE-G3,1,Optical_Core_U3
U4,XPDV4120R High-Speed Photodetector Bank,Finisar,XPDV4120R,1,Detector_Bank_U4
U8,MPT5000 TEC Driver,Melexis,MPT5000,1,TEC_Driver_U8
U9,BCM84881 Controller (FPGA/SerDes),Broadcom,BCM84881,1,BCM84881_BGA
J1,PCIe Gen5 x16 Edge Connector,TE Connectivity,2013289-6,1,PCIe_x16_Edge
MPO1,MPO Input Fiber Array Connector,US Conec,MPO-12-IN,1,MPO_Array
MPO2,MPO Output Fiber Array Connector,US Conec,MPO-12-OUT,1,MPO_Array
C1,0603 MLCC 0.1uF 10V X5R,Murata,GRM188R61A104KA01D,1,C_0603_1608Metric
C2,0603 MLCC 0.1uF 10V X5R,Murata,GRM188R61A104KA01D,1,C_0603_1608Metric
C3,0603 MLCC 0.1uF 10V X5R,Murata,GRM188R61A104KA01D,1,C_0603_1608Metric
C4,0603 MLCC 0.1uF 10V X5R,Murata,GRM188R61A104KA01D,1,C_0603_1608Metric
C5,0603 MLCC 0.1uF 10V X5R,Murata,GRM188R61A104KA01D,1,C_0603_1608Metric
C6,0603 MLCC 0.1uF 10V X5R,Murata,GRM188R61A104KA01D,1,C_0603_1608Metric
C7,0603 MLCC 0.1uF 10V X5R,Murata,GRM188R61A104KA01D,1,C_0603_1608Metric
C8,0603 MLCC 0.1uF 10V X5R,Murata,GRM188R61A104KA01D,1,C_0603_1608Metric
C9,0603 MLCC 0.1uF 10V X5R,Murata,GRM188R61A104KA01D,1,C_0603_1608Metric
C10,0603 MLCC 0.1uF 10V X5R,Murata,GRM188R61A104KA01D,1,C_0603_1608Metric
C11,0603 MLCC 0.1uF 10V X5R,Murata,GRM188R61A104KA01D,1,C_0603_1608Metric
C12,0603 MLCC 0.1uF 10V X5R,Murata,GRM188R61A104KA01D,1,C_0603_1608Metric
C13,0603 MLCC 0.1uF 10V X5R,Murata,GRM188R61A104KA01D,1,C_0603_1608Metric
C14,0603 MLCC 0.1uF 10V X5R,Murata,GRM188R61A104KA01D,1,C_0603_1608Metric
C15,0603 MLCC 0.1uF 10V X5R,Murata,GRM188R61A104KA01D,1,C_0603_1608Metric
C16,0603 MLCC 0.1uF 10V X5R,Murata,GRM188R61A104KA01D,1,C_0603_1608Metric
C17,0603 MLCC 0.1uF 10V X5R,Murata,GRM188R61A104KA01D,1,C_0603_1608Metric
C18,0603 MLCC 0.1uF 10V X5R,Murata,GRM188R61A104KA01D,1,C_0603_1608Metric
C19,0603 MLCC 0.1uF 10V X5R,Murata,GRM188R61A104KA01D,1,C_0603_1608Metric
C20,0603 MLCC 0.1uF 10V X5R,Murata,GRM188R61A104KA01D,1,C_0603_1608Metric
C21,0603 MLCC 0.1uF 10V X5R,Murata,GRM188R61A104KA01D,1,C_0603_1608Metric
C22,0603 MLCC 0.1uF 10V X5R,Murata,GRM188R61A104KA01D,1,C_0603_1608Metric
C23,0603 MLCC 0.1uF 10V X5R,Murata,GRM188R61A104KA01D,1,C_0603_1608Metric
C24,0603 MLCC 0.1uF 10V X5R,Murata,GRM188R61A104KA01D,1,C_0603_1608Metric
C25,0603 MLCC 0.1uF 10V X5R,Murata,GRM188R61A104KA01D,1,C_0603_1608Metric
C26,0603 MLCC 0.1uF 10V X5R,Murata,GRM188R61A104KA01D,1,C_0603_1608Metric
C27,0603 MLCC 0.1uF 10V X5R,Murata,GRM188R61A104KA01D,1,C_0603_1608Metric
C28,0603 MLCC 0.1uF 10V X5R,Murata,GRM188R61A104KA01D,1,C_0603_1608Metric
C29,0603 MLCC 0.1uF 10V X5R,Murata,GRM188R61A104KA01D,1,C_0603_1608Metric
C30,0603 MLCC 0.1uF 10V X5R,Murata,GRM188R61A104KA01D,1,C_0603_1608Metric
C31,0603 MLCC 0.1uF 10V X5R,Murata,GRM188R61A104KA01D,1,C_0603_1608Metric
C32,0603 MLCC 0.1uF 10V X5R,Murata,GRM188R61A104KA01D,1,C_0603_1608Metric
C33,0603 MLCC 0.1uF 10V X5R,Murata,GRM188R61A104KA01D,1,C_0603_1608Metric
C34,0603 MLCC 0.1uF 10V X5R,Murata,GRM188R61A104KA01D,1,C_0603_1608Metric
C35,0603 MLCC 0.1uF 10V X5R,Murata,GRM188R61A104KA01D,1,C_0603_1608Metric
C36,0603 MLCC 0.1uF 10V X5R,Murata,GRM188R61A104KA01D,1,C_0603_1608Metric
C37,0603 MLCC 0.1uF 10V X5R,Murata,GRM188R61A104KA01D,1,C_0603_1608Metric
C38,0603 MLCC 0.1uF 10V X5R,Murata,GRM188R61A104KA01D,1,C_0603_1608Metric
C39,0603 MLCC 0.1uF 10V X5R,Murata,GRM188R61A104KA01D,1,C_0603_1608Metric
C40,0603 MLCC 0.1uF 10V X5R,Murata,GRM188R61A104KA01D,1,C_0603_1608Metric
C41,0603 MLCC 0.1uF 10V X5R,Murata,GRM188R61A104KA01D,1,C_0603_1608Metric
C42,0603 MLCC 0.1uF 10V X5R,Murata,GRM188R61A104KA01D,1,C_0603_1608Metric
C43,0603 MLCC 0.1uF 10V X5R,Murata,GRM188R61A104KA01D,1,C_0603_1608Metric
C44,0603 MLCC 0.1uF 10V X5R,Murata,GRM188R61A104KA01D,1,C_0603_1608Metric
C45,0603 MLCC 0.1uF 10V X5R,Murata,GRM188R61A104KA01D,1,C_0603_1608Metric
C46,0603 MLCC 0.1uF 10V X5R,Murata,GRM188R61A104KA01D,1,C_0603_1608Metric
C47,0603 MLCC 0.1uF 10V X5R,Murata,GRM188R61A104KA01D,1,C_0603_1608Metric
C48,0603 MLCC 0.1uF 10V X5R,Murata,GRM188R61A104KA01D,1,C_0603_1608Metric
C49,0603 MLCC 0.1uF 10V X5R,Murata,GRM188R61A104KA01D,1,C_0603_1608Metric
C50,0603 MLCC 0.1uF 10V X5R,Murata,GRM188R61A104KA01D,1,C_0603_1608Metric
C51,0603 MLCC 0.1uF 10V X5R,Murata,GRM188R61A104KA01D,1,C_0603_1608Metric
C52,0603 MLCC 0.1uF 10V X5R,Murata,GRM188R61A104KA01D,1,C_0603_1608Metric
C53,0603 MLCC 0.1uF 10V X5R,Murata,GRM188R61A104KA01D,1,C_0603_1608Metric
C54,0603 MLCC 0.1uF 10V X5R,Murata,GRM188R61A104KA01D,1,C_0603_1608Metric
C55,0603 MLCC 0.1uF 10V X5R,Murata,GRM188R61A104KA01D,1,C_0603_1608Metric
C56,0603 MLCC 0.1uF 10V X5R,Murata,GRM188R61A104KA01D,1,C_0603_1608Metric
C57,0603 MLCC 0.1uF 10V X5R,Murata,GRM188R61A104KA01D,1,C_0603_1608Metric
C58,0603 MLCC 0.1uF 10V X5R,Murata,GRM188R61A104KA01D,1,C_0603_1608Metric
C59,0603 MLCC 0.1uF 10V X5R,Murata,GRM188R61A104KA01D,1,C_0603_1608Metric
C60,0603 MLCC 0.1uF 10V X5R,Murata,GRM188R61A104KA01D,1,C_0603_1608Metric
C61,0603 MLCC 0.1uF 10V X5R,Murata,GRM188R61A104KA01D,1,C_0603_1608Metric
C62,0603 MLCC 0.1uF 10V X5R,Murata,GRM188R61A104KA01D,1,C_0603_1608Metric
C63,0603 MLCC 0.1uF 10V X5R,Murata,GRM188R61A104KA01D,1,C_0603_1608Metric
C64,0603 MLCC 0.1uF 10V X5R,Murata,GRM188R61A104KA01D,1,C_0603_1608Metric
C65,0603 MLCC 0.1uF 10V X5R,Murata,GRM188R61A104KA01D,1,C_0603_1608Metric
C66,0603 MLCC 0.1uF 10V X5R,Murata,GRM188R61A104KA01D,1,C_0603_1608Metric
C67,0603 MLCC 0.1uF 10V X5R,Murata,GRM188R61A104KA01D,1,C_0603_1608Metric
C68,0603 MLCC 0.1uF 10V X5R,Murata,GRM188R61A104KA01D,1,C_0603_1608Metric
C69,0603 MLCC 0.1uF 10V X5R,Murata,GRM188R61A104KA01D,1,C_0603_1608Metric
C70,0603 MLCC 0.1uF 10V X5R,Murata,GRM188R61A104KA01D,1,C_0603_1608Metric
C71,0603 MLCC 0.1uF 10V X5R,Murata,GRM188R61A104KA01D,1,C_0603_1608Metric
C72,0603 MLCC 0.1uF 10V X5R,Murata,GRM188R61A104KA01D,1,C_0603_1608Metric
C73,0603 MLCC 0.1uF 10V X5R,Murata,GRM188R61A104KA01D,1,C_0603_1608Metric
C74,0603 MLCC 0.1uF 10V X5R,Murata,GRM188R61A104KA01D,1,C_0603_1608Metric
C75,0603 MLCC 0.1uF 10V X5R,Murata,GRM188R61A104KA01D,1,C_0603_1608Metric
C76,0603 MLCC 0.1uF 10V X5R,Murata,GRM188R61A104KA01D,1,C_0603_1608Metric
C77,0603 MLCC 0.1uF 10V X5R,Murata,GRM188R61A104KA01D,1,C_0603_1608Metric
C78,0603 MLCC 0.1uF 10V X5R,Murata,GRM188R61A104KA01D,1,C_0603_1608Metric
C79,0603 MLCC 0.1uF 10V X5R,Murata,GRM188R61A104KA01D,1,C_0603_1608Metric
C80,0603 MLCC 0.1uF 10V X5R,Murata,GRM188R61A104KA01D,1,C_0603_1608Metric
C81,0603 MLCC 0.1uF 10V X5R,Murata,GRM188R61A104KA01D,1,C_0603_1608Metric
C82,0603 MLCC 0.1uF 10V X5R,Murata,GRM188R61A104KA01D,1,C_0603_1608Metric
C83,0603 MLCC 0.1uF 10V X5R,Murata,GRM188R61A104KA01D,1,C_0603_1608Metric
C84,0603 MLCC 0.1uF 10V X5R,Murata,GRM188R61A104KA01D,1,C_0603_1608Metric
C85,0603 MLCC 0.1uF 10V X5R,Murata,GRM188R61A104KA01D,1,C_0603_1608Metric
C86,0603 MLCC 0.1uF 10V X5R,Murata,GRM188R61A104KA01D,1,C_0603_1608Metric
C87,0603 MLCC 0.1uF 10V X5R,Murata,GRM188R61A104KA01D,1,C_0603_1608Metric
C88,0603 MLCC 0.1uF 10V X5R,Murata,GRM188R61A104KA01D,1,C_0603_1608Metric
C89,0603 MLCC 0.1uF 10V X5R,Murata,GRM188R61A104KA01D,1,C_0603_1608Metric
C90,0603 MLCC 0.1uF 10V X5R,Murata,GRM188R61A104KA01D,1,C_0603_1608Metric
C91,0603 MLCC 0.1uF 10V X5R,Murata,GRM188R61A104KA01D,1,C_0603_1608Metric
C92,0603 MLCC 0.1uF 10V X5R,Murata,GRM188R61A104KA01D,1,C_0603_1608Metric
C93,0603 MLCC 0.1uF 10V X5R,Murata,GRM188R61A104KA01D,1,C_0603_1608Metric
C94,0603 MLCC 0.1uF 10V X5R,Murata,GRM188R61A104KA01D,1,C_0603_1608Metric
C95,0603 MLCC 0.1uF 10V X5R,Murata,GRM188R61A104KA01D,1,C_0603_1608Metric
C96,0603 MLCC 0.1uF 10V X5R,Murata,GRM188R61A104KA01D,1,C_0603_1608Metric
C97,0603 MLCC 0.1uF 10V X5R,Murata,GRM188R61A104KA01D,1,C_0603_1608Metric
C98,0603 MLCC 0.1uF 10V X5R,Murata,GRM188R61A104KA01D,1,C_0603_1608Metric
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
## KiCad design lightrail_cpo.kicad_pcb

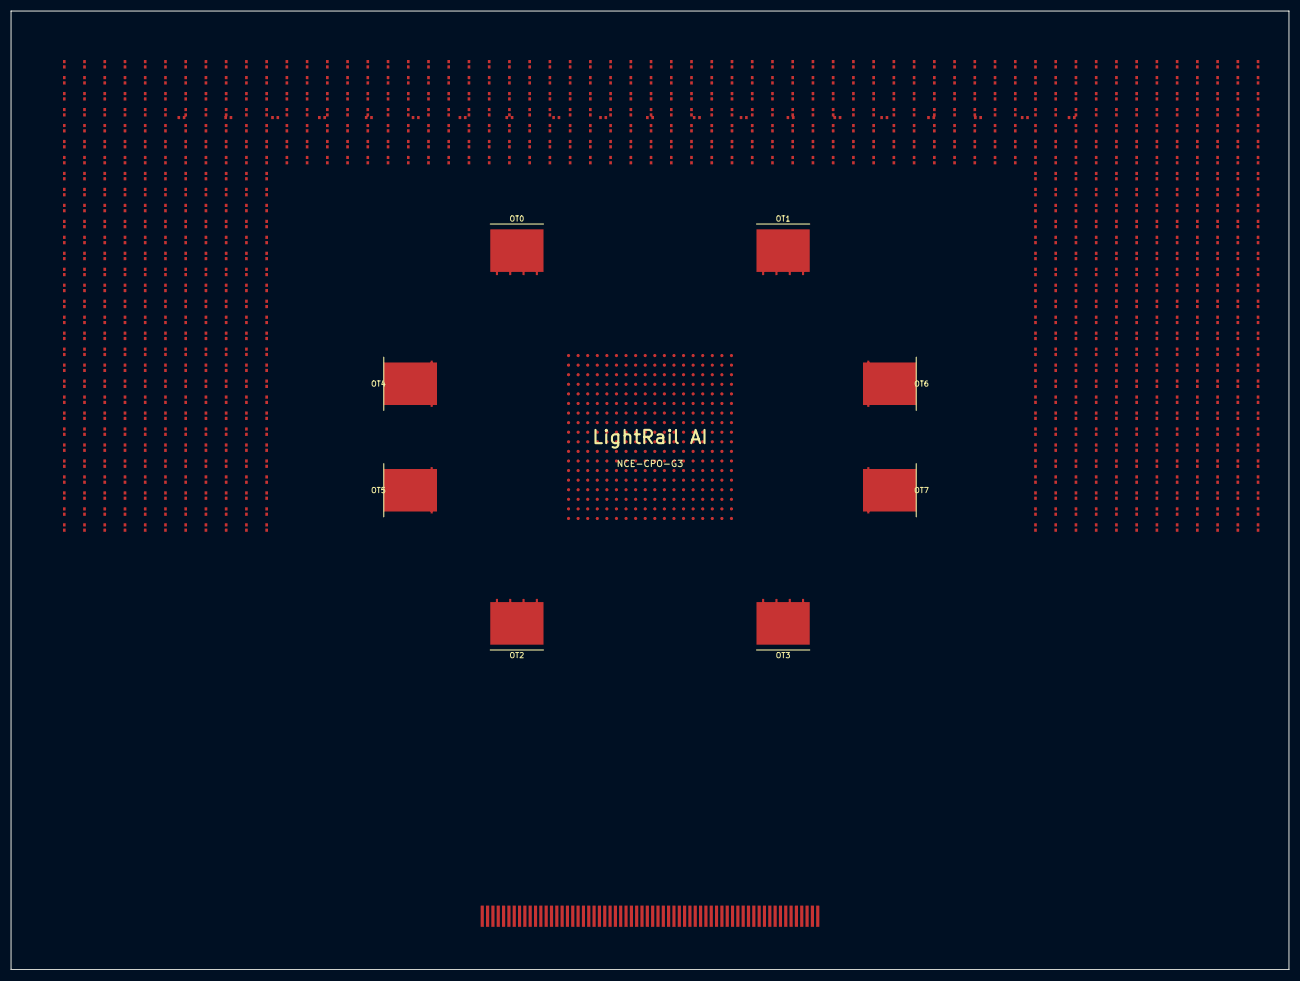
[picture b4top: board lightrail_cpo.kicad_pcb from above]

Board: 15 copper layers, 240.0 x 180.0 mm, 9 parts (0 on the bottom side), 10 nets, no tracks yet.

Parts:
LightRail AI: NCE-CPO-G3; NCE_CORE_BGA
OT0, OT1, OT2, OT3, OT4, OT5, OT6, OT7: O_TILE_TFLN

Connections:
GND: LightRail AI.7_2, LightRail AI.7_3, LightRail AI.7_4, LightRail AI.7_5, LightRail AI.7_6, LightRail AI.7_7, LightRail AI.7_8, LightRail AI.7_9, LightRail AI.7_10, LightRail AI.7_11, LightRail AI.7_12, LightRail AI.7_13, LightRail AI.7_14, LightRail AI.7_15, LightRail AI.7_16, LightRail AI.7_17, LightRail AI.8_0, LightRail AI.8_1, LightRail AI.8_2, LightRail AI.8_3, LightRail AI.8_4, LightRail AI.8_5, LightRail AI.8_6, LightRail AI.8_7, LightRail AI.8_10, LightRail AI.8_11, LightRail AI.8_12, LightRail AI.8_13, LightRail AI.8_14, LightRail AI.8_15, LightRail AI.8_16, LightRail AI.8_17, LightRail AI.9_0, LightRail AI.9_1, LightRail AI.9_2, LightRail AI.9_3, LightRail AI.9_4, LightRail AI.9_5, LightRail AI.9_6, LightRail AI.9_7, LightRail AI.9_10, LightRail AI.9_11, LightRail AI.9_12, LightRail AI.9_13, LightRail AI.9_14, LightRail AI.9_15, LightRail AI.9_16, LightRail AI.9_17, LightRail AI.10_0, LightRail AI.10_1, LightRail AI.10_2, LightRail AI.10_3, LightRail AI.10_4, LightRail AI.10_5, LightRail AI.10_6, LightRail AI.10_7, LightRail AI.10_8, LightRail AI.10_9, LightRail AI.10_10, LightRail AI.10_11, LightRail AI.10_12, LightRail AI.10_13, LightRail AI.10_14, LightRail AI.10_15, LightRail AI.10_16, LightRail AI.10_17, LightRail AI.11_0, LightRail AI.11_1, LightRail AI.11_2, LightRail AI.11_3, LightRail AI.11_4, LightRail AI.11_5, LightRail AI.11_6, LightRail AI.11_7, LightRail AI.11_8, LightRail AI.11_9, LightRail AI.11_10, LightRail AI.11_11, LightRail AI.11_12, LightRail AI.11_13, LightRail AI.11_14, LightRail AI.11_15, LightRail AI.11_16, LightRail AI.11_17, LightRail AI.12_0, LightRail AI.12_1, LightRail AI.12_2, LightRail AI.12_3, LightRail AI.12_4, LightRail AI.12_5, LightRail AI.12_6, LightRail AI.12_7, LightRail AI.12_8, LightRail AI.12_9, LightRail AI.12_10, LightRail AI.12_11, LightRail AI.12_12, LightRail AI.12_13, LightRail AI.12_14, LightRail AI.12_15, LightRail AI.12_16, LightRail AI.12_17, LightRail AI.13_0, LightRail AI.13_1, LightRail AI.13_2, LightRail AI.13_3, LightRail AI.13_4, LightRail AI.13_5, LightRail AI.13_6, LightRail AI.13_7, LightRail AI.13_8, LightRail AI.13_9, LightRail AI.13_10, LightRail AI.13_11, LightRail AI.13_12, LightRail AI.13_13, LightRail AI.13_14, LightRail AI.13_15, LightRail AI.13_16, LightRail AI.13_17, LightRail AI.14_0, LightRail AI.14_1, LightRail AI.14_2, LightRail AI.14_3, LightRail AI.14_4, LightRail AI.14_5, LightRail AI.14_6, LightRail AI.14_7, LightRail AI.14_8, LightRail AI.14_9, LightRail AI.14_10, LightRail AI.14_11, LightRail AI.14_12, LightRail AI.14_13, LightRail AI.14_14, LightRail AI.14_15, LightRail AI.14_16, LightRail AI.14_17, LightRail AI.15_0, LightRail AI.15_1, LightRail AI.15_2, LightRail AI.15_3, LightRail AI.15_4, LightRail AI.15_5, LightRail AI.15_6, LightRail AI.15_7, LightRail AI.15_8, LightRail AI.15_9, LightRail AI.15_10, LightRail AI.15_11, LightRail AI.15_12, LightRail AI.15_13, LightRail AI.15_14, LightRail AI.15_15, LightRail AI.15_16, LightRail AI.15_17, LightRail AI.16_0, LightRail AI.16_1, LightRail AI.16_2, LightRail AI.16_3, LightRail AI.16_4, LightRail AI.16_5, LightRail AI.16_6, LightRail AI.16_7, LightRail AI.16_8, LightRail AI.16_9, LightRail AI.16_10, LightRail AI.16_11, LightRail AI.16_12, LightRail AI.16_13, LightRail AI.16_14, LightRail AI.16_15, LightRail AI.16_16, LightRail AI.16_17, LightRail AI.17_0, LightRail AI.17_1, LightRail AI.17_2, LightRail AI.17_3, LightRail AI.17_4, LightRail AI.17_5, LightRail AI.17_6, LightRail AI.17_7, LightRail AI.17_8, LightRail AI.17_9, LightRail AI.17_10, LightRail AI.17_11, LightRail AI.17_12, LightRail AI.17_13, LightRail AI.17_14, LightRail AI.17_15, LightRail AI.17_16, LightRail AI.17_17, OT0.TH, OT1.TH, OT2.TH, OT3.TH, OT4.TH, OT5.TH, OT6.TH, OT7.TH
O_TILE_0_RF_0: LightRail AI.3_10, LightRail AI.4_0, LightRail AI.4_8, LightRail AI.4_16, LightRail AI.5_6, LightRail AI.5_14, LightRail AI.6_4, LightRail AI.6_12, OT0.RF0
O_TILE_1_RF_1: LightRail AI.3_11, LightRail AI.4_1, LightRail AI.4_9, LightRail AI.4_17, LightRail AI.5_7, LightRail AI.5_15, LightRail AI.6_5, LightRail AI.6_13, OT1.RF1
O_TILE_2_RF_2: LightRail AI.3_12, LightRail AI.4_2, LightRail AI.4_10, LightRail AI.5_0, LightRail AI.5_8, LightRail AI.5_16, LightRail AI.6_6, LightRail AI.6_14, OT2.RF2
O_TILE_3_RF_3: LightRail AI.3_13, LightRail AI.4_3, LightRail AI.4_11, LightRail AI.5_1, LightRail AI.5_9, LightRail AI.5_17, LightRail AI.6_7, LightRail AI.6_15, OT3.RF3
O_TILE_4_RF_0: LightRail AI.3_14, LightRail AI.4_4, LightRail AI.4_12, LightRail AI.5_2, LightRail AI.5_10, LightRail AI.6_0, LightRail AI.6_8, LightRail AI.6_16, OT4.RF0
O_TILE_5_RF_1: LightRail AI.3_15, LightRail AI.4_5, LightRail AI.4_13, LightRail AI.5_3, LightRail AI.5_11, LightRail AI.6_1, LightRail AI.6_9, LightRail AI.6_17, OT5.RF1
O_TILE_6_RF_2: LightRail AI.3_16, LightRail AI.4_6, LightRail AI.4_14, LightRail AI.5_4, LightRail AI.5_12, LightRail AI.6_2, LightRail AI.6_10, LightRail AI.7_0, OT6.RF2
O_TILE_7_RF_3: LightRail AI.3_17, LightRail AI.4_7, LightRail AI.4_15, LightRail AI.5_5, LightRail AI.5_13, LightRail AI.6_3, LightRail AI.6_11, LightRail AI.7_1, OT7.RF3
VCC_1V0: LightRail AI.8_8, LightRail AI.8_9, LightRail AI.9_8, LightRail AI.9_9
